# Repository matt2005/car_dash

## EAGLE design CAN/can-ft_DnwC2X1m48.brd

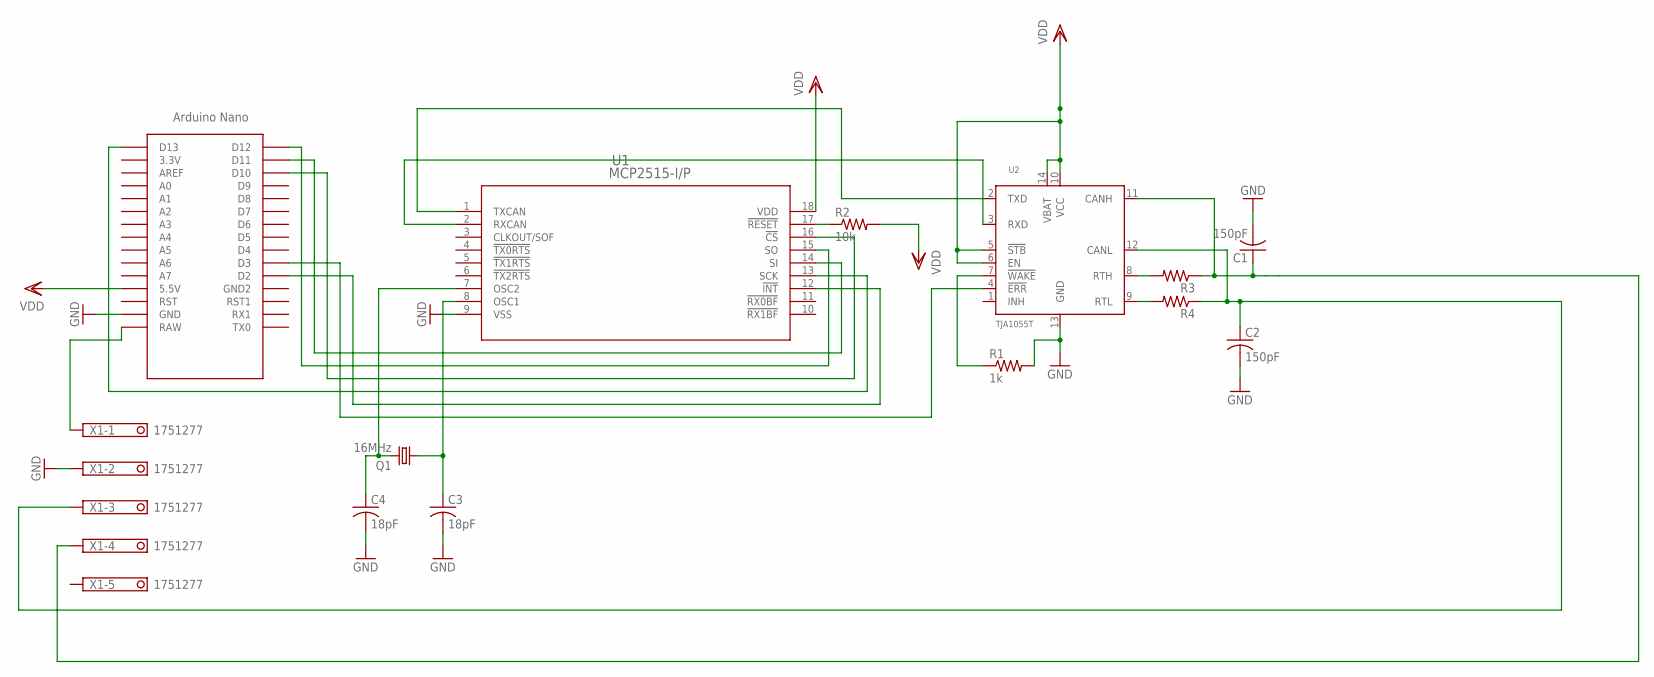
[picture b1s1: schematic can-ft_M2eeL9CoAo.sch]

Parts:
C1, C2: 150pF; C050-025X075
C3, C4: 18pF; C050-025X075
Q1: 16MHz; HC49/S
R1: 1k; 0207/7
R2: 10k; 0207/7
R3, R4: R-US_0207/7; 0207/7
U1: MCP2515-I/P; PDIP18_300MC_MCH
U2: TJA1055T; SOT108-1
U$1: NANO
X1: 1751277

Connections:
GND: C1.2, C2.2, C3.2, C4.2, R1.2, U1.9 (VSS), U2.13 (GND), U$1.GND, X1.2
unnamed: U1.1 (TXCAN), U2.2 (TXD)
unnamed: U1.2 (RXCAN), U2.3 (RXD)
unnamed: R3.2, U2.8 (RTH)
unnamed: R4.2, U2.9 (RTL)
unnamed: C1.1, R3.1, U2.11 (CANH), X1.4
unnamed: C2.1, R4.1, U2.12 (CANL), X1.3
unnamed: U1.15 (SO), U$1.D12
unnamed: R1.1, U2.7 (!WAKE)
unnamed: U1.14 (SI), U$1.D11
unnamed: U1.16 (!CS), U$1.D10
unnamed: U1.13 (SCK), U$1.D13
unnamed: U1.12 (!INT), U$1.D2
unnamed: U2.4 (!ERR), U$1.D3
unnamed: R2.1, U1.17 (!RESET)
unnamed: C4.1, Q1.2, U1.7 (OSC2)
unnamed: C3.1, Q1.1, U1.8 (OSC1)
unnamed: U$1.RAW, X1.1
VDD: R2.2, U1.18 (VDD), U2.5 (!STB), U2.6 (EN), U2.10 (VCC), U2.14 (VBAT), U$1.5V (5.5V)

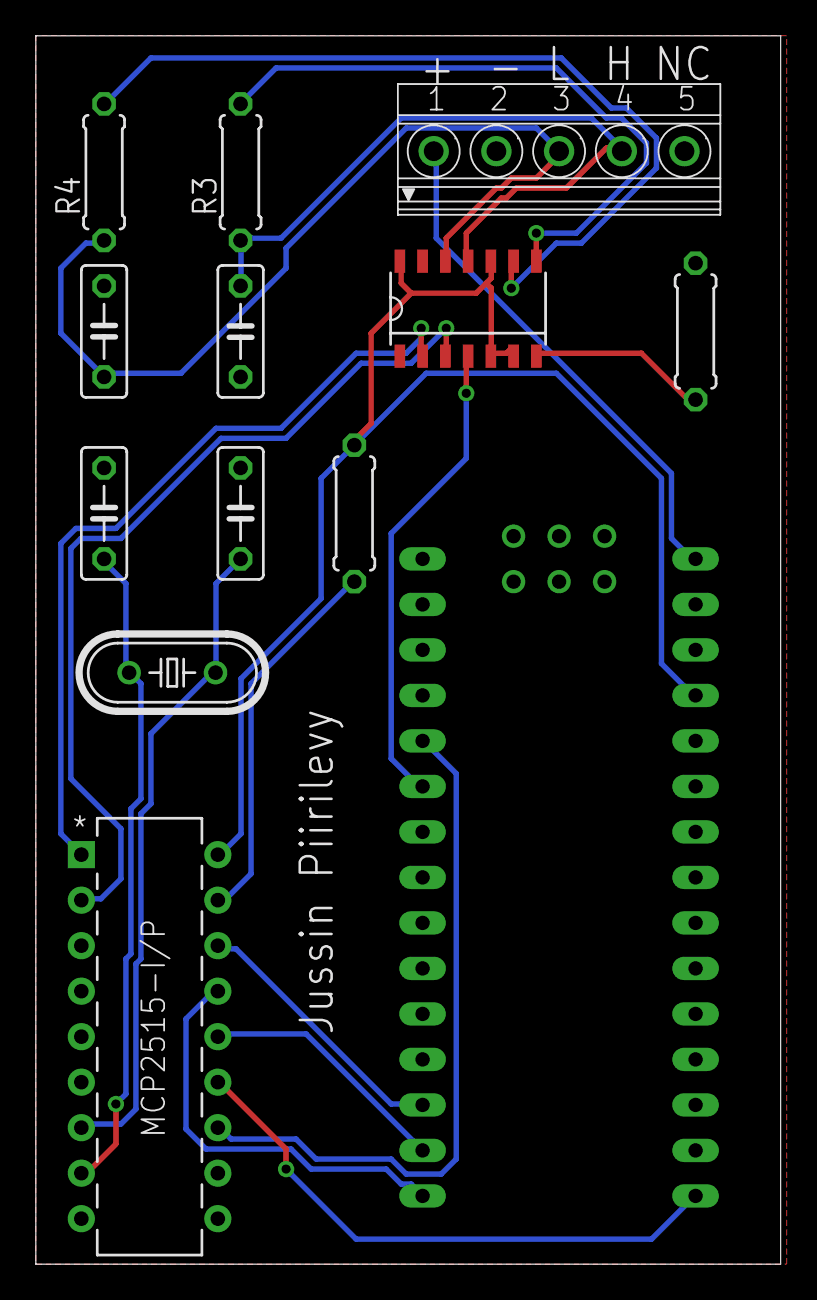
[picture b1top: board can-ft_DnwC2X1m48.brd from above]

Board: 2 copper layers, 41.6 x 68.6 mm, 13 parts (0 on the bottom side), 19 nets.

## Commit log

2021-01-27 added files

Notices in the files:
parts and their libraries:
NXP_60_26022015: This library may be distributed and adapted freely for any purpose, as long as NXP is credited and any new creation is licensed under the same terms.
